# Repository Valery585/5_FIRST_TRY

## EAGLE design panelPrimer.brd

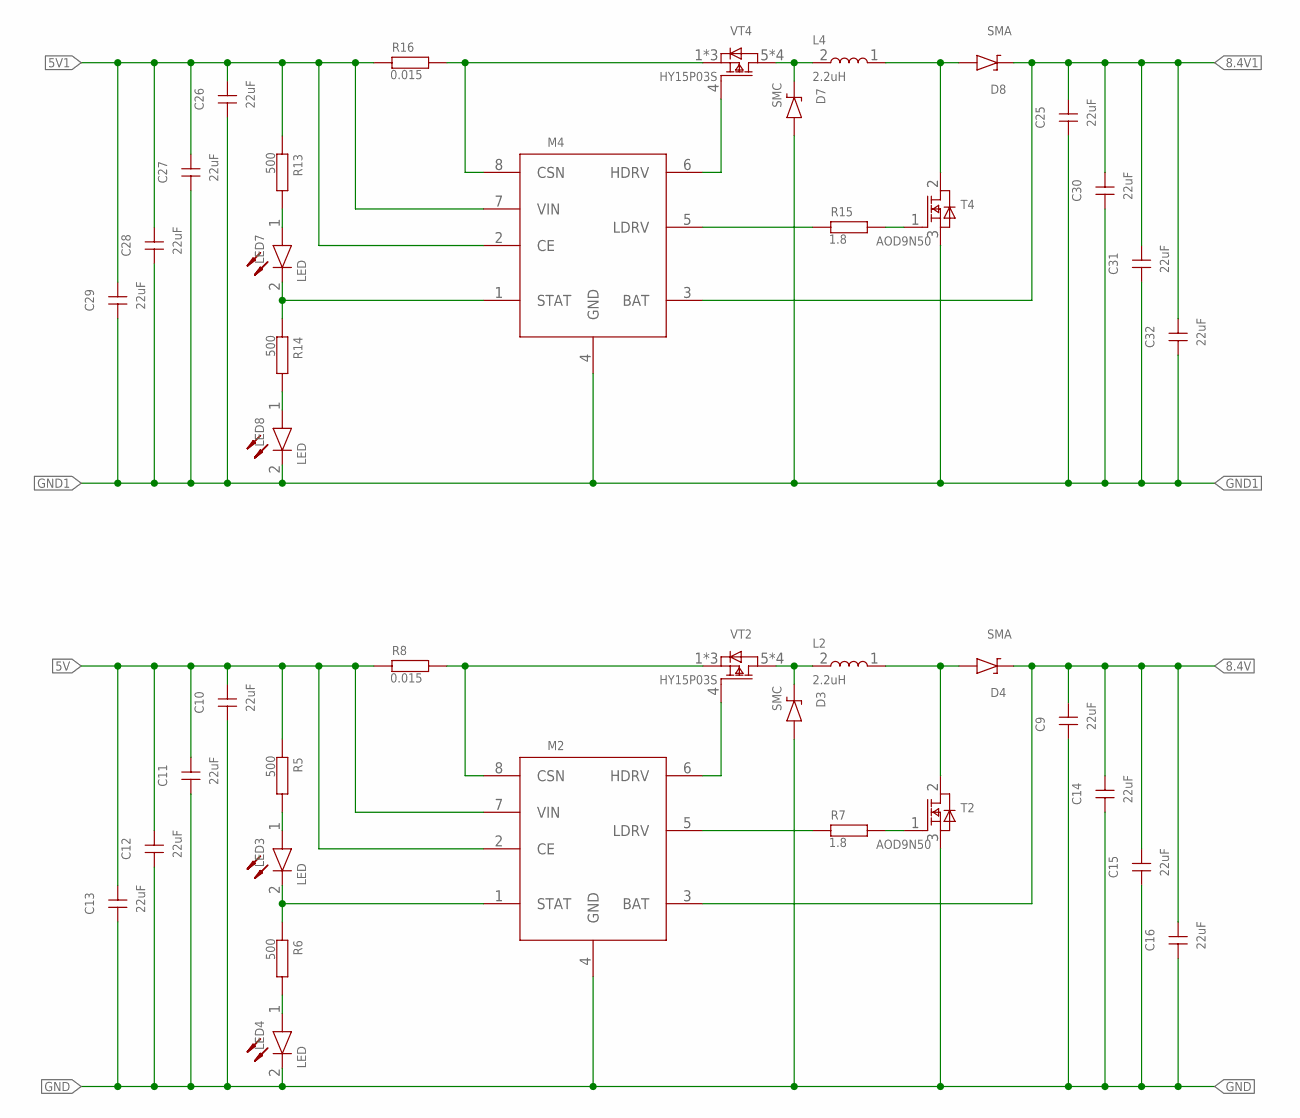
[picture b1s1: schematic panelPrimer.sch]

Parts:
C9, C10, C11, C12, C13, C14, C15, C16, C25, C26, C27, C28, C29, C30, C31, C32: 22uF; 1206
D3, D7: SMC
D4, D8: SMA
L2, L4: 2.2uH; FXL0530
LED3, LED4, LED7, LED8: LED
M2, M4: CN3302SOP-8; SOP-8
R5, R6, R13, R14: 500; 0603
R7, R15: 1.8; 0603
R8, R16: 0.015; 2512
T2, T4: AOD9N50; DRACK
VT2, VT4: HY15P03S; SOP-8

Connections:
5V: C10.2, C11.2, C12.2, C13.2, M2.2 (CE), M2.7 (VIN), R5.1, R8.1
5V1: C26.2, C27.2, C28.2, C29.2, M4.2 (CE), M4.7 (VIN), R13.1, R16.1
8.4V: C9.2, C14.2, C15.2, C16.2, D4.2 (C), M2.3 (BAT)
8.4V1: C25.2, C30.2, C31.2, C32.2, D8.2 (C), M4.3 (BAT)
GND: C9.1, C10.1, C11.1, C12.1, C13.1, C14.1, C15.1, C16.1, D3.1 (A), LED4.2 (CATHODE), M2.4 (GND), T2.3 (S)
GND1: C25.1, C26.1, C27.1, C28.1, C29.1, C30.1, C31.1, C32.1, D7.1 (A), LED8.2 (CATHODE), M4.4 (GND), T4.3 (S)
unnamed: LED3.1 (ANODE), R5.2
unnamed: LED4.1 (ANODE), R6.2
unnamed: M2.5 (LDRV), R7.1
unnamed: M2.8 (CSN), R8.2, VT2.1 (S), VT2.2 (S), VT2.3 (S)
unnamed: R7.2, T2.1 (G)
unnamed: D3.2 (C), L2.2, VT2.5 (D), VT2.6 (D), VT2.7 (D), VT2.8 (D)
unnamed: D4.1 (A), L2.1, T2.2 (D)
unnamed: LED3.2 (CATHODE), M2.1 (STAT), R6.1
unnamed: M2.6 (HDRV), VT2.4 (G)
unnamed: LED7.1 (ANODE), R13.2
unnamed: LED8.1 (ANODE), R14.2
unnamed: M4.5 (LDRV), R15.1
unnamed: M4.8 (CSN), R16.2, VT4.1 (S), VT4.2 (S), VT4.3 (S)
unnamed: R15.2, T4.1 (G)
unnamed: D7.2 (C), L4.2, VT4.5 (D), VT4.6 (D), VT4.7 (D), VT4.8 (D)
unnamed: D8.1 (A), L4.1, T4.2 (D)
unnamed: LED7.2 (CATHODE), M4.1 (STAT), R14.1
unnamed: M4.6 (HDRV), VT4.4 (G)

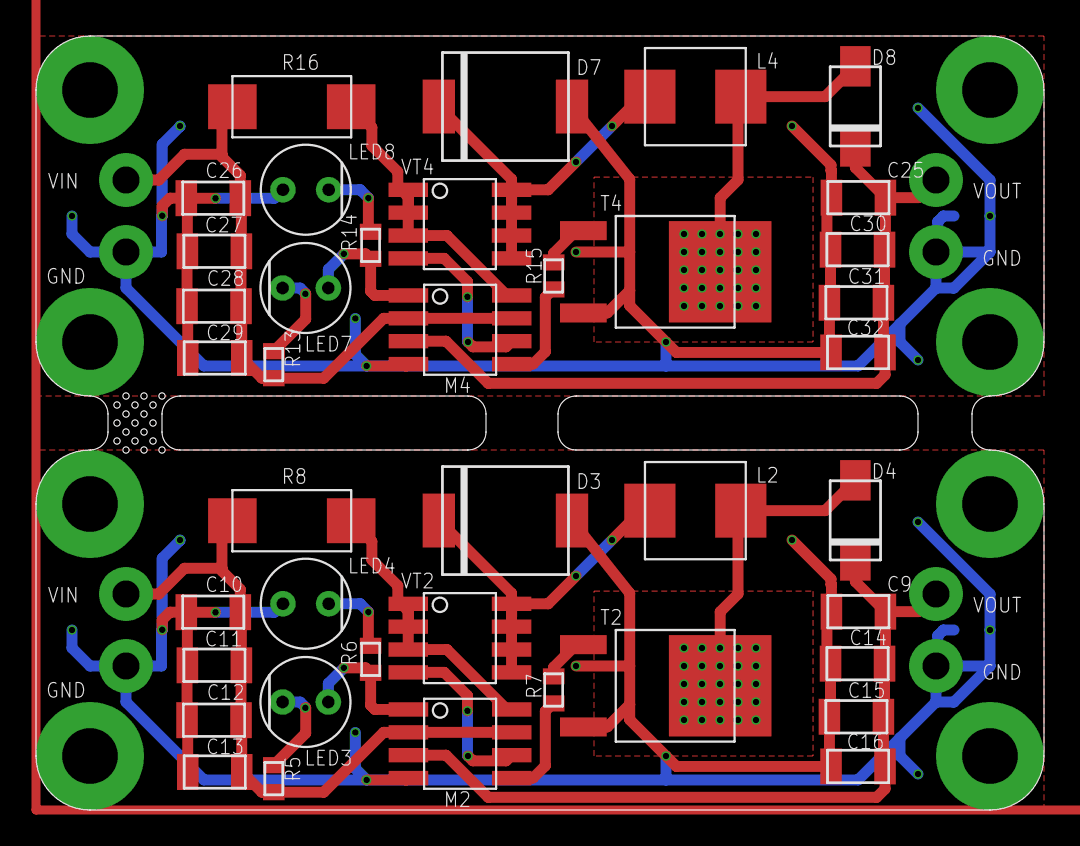
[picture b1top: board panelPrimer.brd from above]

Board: 2 copper layers, 56.0 x 43.0 mm, 40 parts (0 on the bottom side), 24 nets.

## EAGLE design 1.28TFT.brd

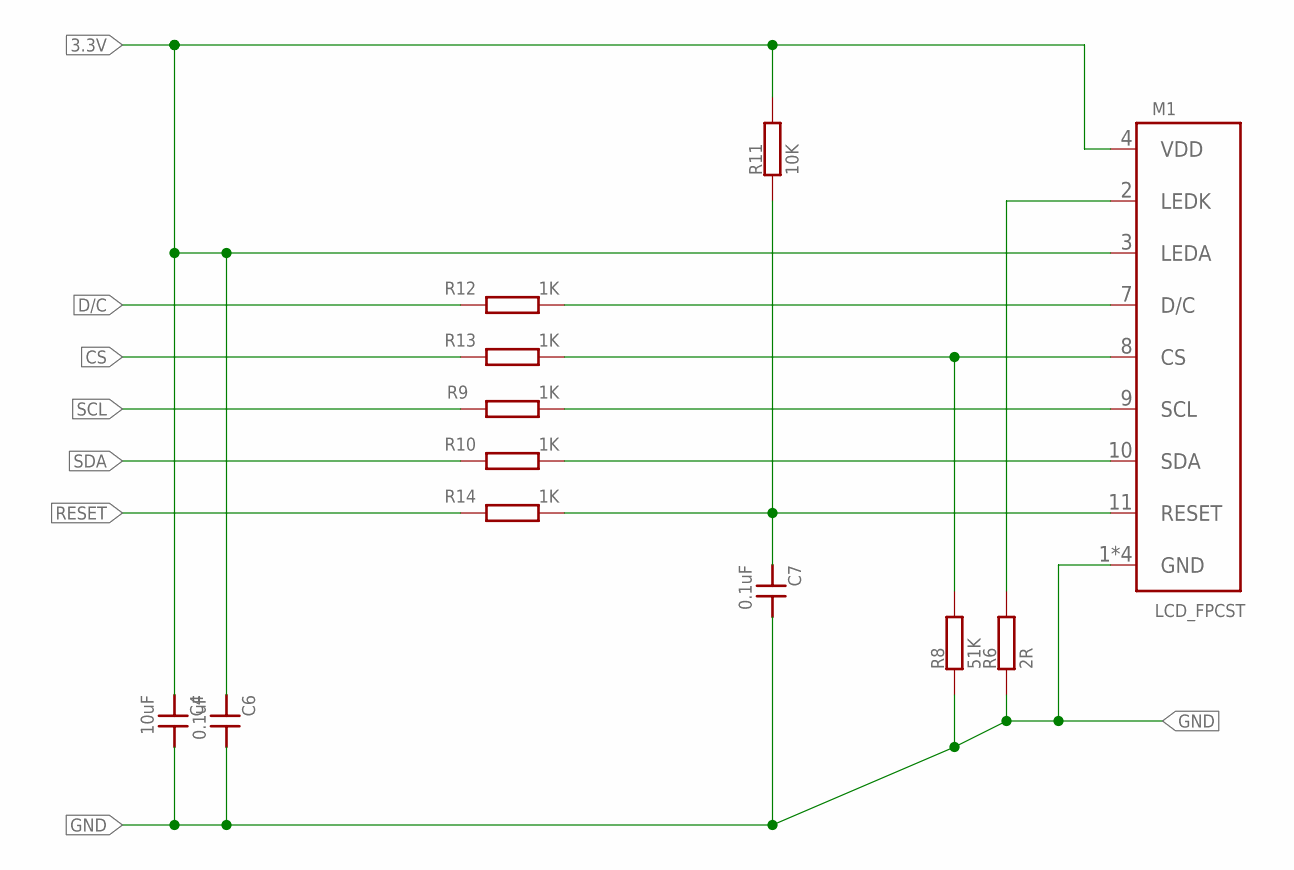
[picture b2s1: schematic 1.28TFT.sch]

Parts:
C4: 10uF; 0603
C6, C7: 0.1uF; 0603
M1: LCD_FPCST; FR-128HR01A
R6: 2R; 0603
R8: 51K; 0603
R9, R10, R12, R13, R14: 1K; 0603
R11: 10K; 0603

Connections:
3.3V: C4.P$1, C6.P$1, M1.3 (LEDA), M1.4 (VDD), R11.P$2
CS: R13.P$2
D/C: R12.P$2
GND: C4.P$2, C6.P$2, C7.P$2, M1.1 (GND), M1.5 (GND), M1.6 (GND), M1.12 (GND), R6.P$1, R8.P$1
unnamed: M1.2 (LEDK), R6.P$2
unnamed: M1.8 (CS), R8.P$2, R13.P$1
unnamed: M1.9 (SCL), R9.P$1
unnamed: M1.10 (SDA), R10.P$1
unnamed: M1.7 (D/C), R12.P$1
RESET: R14.P$2
RST: C7.P$1, M1.11 (RESET), R11.P$1, R14.P$1
SCL: R9.P$2
SDA: R10.P$2

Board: 2 copper layers, 12 parts (0 on the bottom side), 8 nets, no tracks yet.

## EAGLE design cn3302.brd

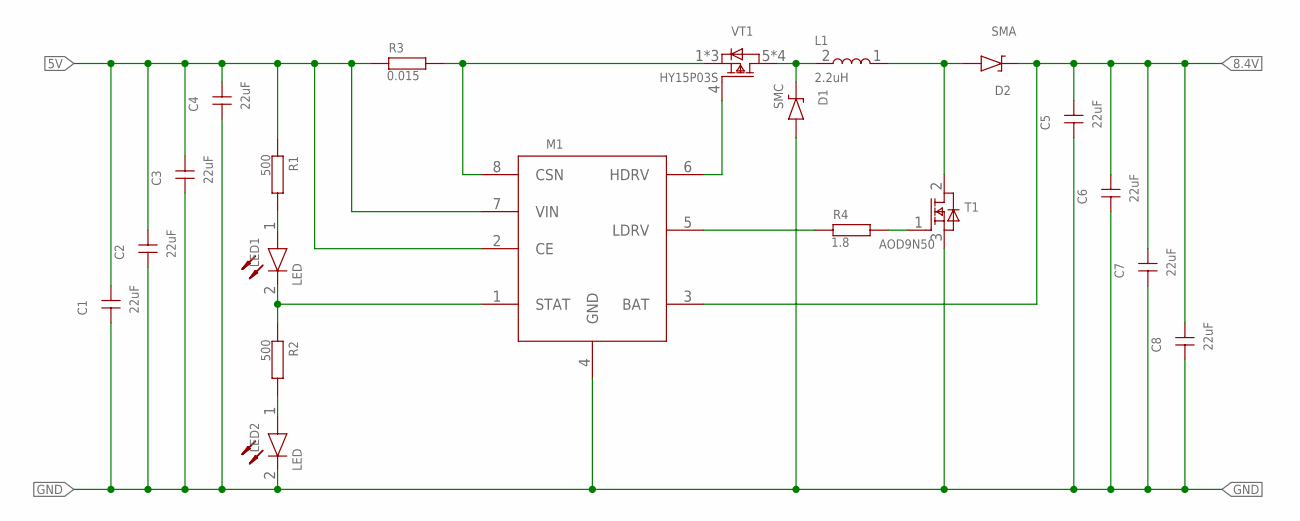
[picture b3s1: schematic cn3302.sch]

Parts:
C1, C2, C3, C4, C5, C6, C7, C8: 22uF; 1206
D1: SMC
D2: SMA
L1: 2.2uH; FXL0530
LED1, LED2: LED
M1: CN3302SOP-8; SOP-8
R1, R2: 500; 0603
R3: 0.015; 2512
R4: 1.8; 0603
T1: AOD9N50; DRACK
VT1: HY15P03S; SOP-8

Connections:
5V: C1.2, C2.2, C3.2, C4.2, M1.2 (CE), M1.7 (VIN), R1.1, R3.1
8.4V: C5.2, C6.2, C7.2, C8.2, D2.2 (C), M1.3 (BAT)
GND: C1.1, C2.1, C3.1, C4.1, C5.1, C6.1, C7.1, C8.1, D1.1 (A), LED2.2 (CATHODE), M1.4 (GND), T1.3 (S)
unnamed: LED1.1 (ANODE), R1.2
unnamed: LED2.1 (ANODE), R2.2
unnamed: M1.6 (HDRV), VT1.4 (G)
unnamed: M1.5 (LDRV), R4.1
unnamed: LED1.2 (CATHODE), M1.1 (STAT), R2.1
unnamed: M1.8 (CSN), R3.2, VT1.1 (S), VT1.2 (S), VT1.3 (S)
unnamed: R4.2, T1.1 (G)
unnamed: D1.2 (C), L1.2, VT1.5 (D), VT1.6 (D), VT1.7 (D), VT1.8 (D)
unnamed: D2.1 (A), L1.1, T1.2 (D)

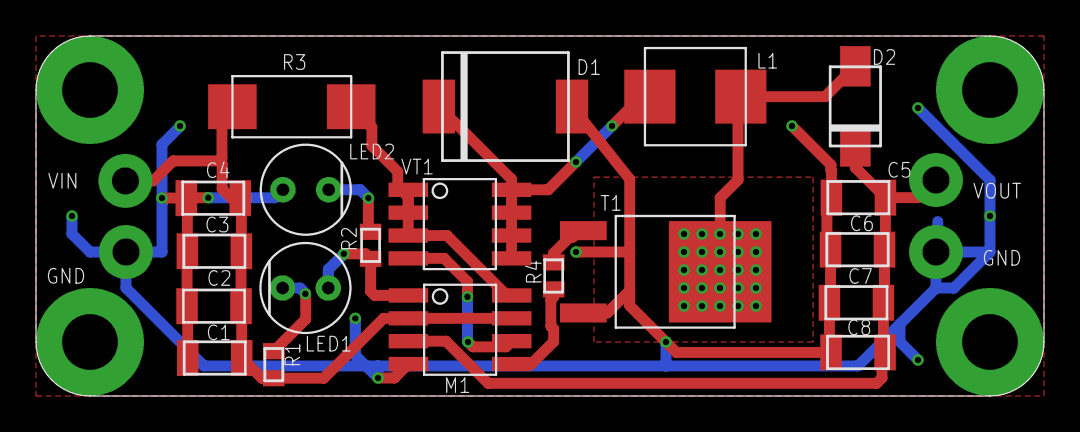
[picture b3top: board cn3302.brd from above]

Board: 2 copper layers, 56.0 x 20.0 mm, 20 parts (0 on the bottom side), 12 nets.

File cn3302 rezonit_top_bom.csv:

Comment,Designator,Footprint,LCSC Part #
 AOD9N50,T1,DRACK,
0.015,R3,2512,
1.8,R4,0603,
2.2uH,L1,FXL0530,
22uF,C1 C2 C3 C4 C5 C6 C7 C8,1206,
500,R1 R2,0603,
CN3302SOP-8,M1,SOP-8,
HY15P03S,VT1,SOP-8,
SMA,D2,SMA,
SMC,D1,SMC,

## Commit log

2023-09-28 Добавил текстовый файл
2023-09-29 Добавил документ xlsx
2023-09-29 испр
2023-09-29 исправил файл xlsx
2023-09-29 Добавил библиотеку транзистора
2023-09-29 Исправил библиотеку my lib
2023-10-02 Добавил в библиотеку my lib.lbr компонент 74HC00
2023-10-02 исправил компонент 74HC00
2023-10-02 Добавил в библиотеку DIP-8 и SOIC-8
2023-10-03 добавил библиотеки транзистор, резистор,конденсатор и диод
2023-10-04 Исправил библиотеки
2023-10-05 Добавил библиотеку LED и MICRO
2023-10-05 поправил УГО диода
2023-10-05 построил схему
2023-10-05 исправил схему
2023-10-05 отредачил схем
2023-10-06 SOBRAL PLATU
2023-10-06 Проложил дорожки
2023-10-06 проложил дорожки на плате
2023-10-06 Исправил плату
2023-10-12 футпринт lid
2023-10-12 пофиксил слегка либу
2023-10-12 adding fold
2023-10-12 BUGFIX
2023-10-18 составил схему, построил плату
2023-10-19 design block
2023-10-20 добавил word
2023-10-20 word
2023-10-30 Исправил word файл
2023-11-09 adding txt & xlsx
2023-11-09 bufgix
2023-11-09 bug fix
